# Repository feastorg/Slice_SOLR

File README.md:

<div align="center">
  <!-- Title: -->
  
  <h2><a href="https://github.com/uwo-fast/Slice_SOLR"> Slice SOLR </a></h2>
  <!-- Labels: -->
  <!-- First row: -->

  <a href="https://certification.oshwa.org/">
    
    <!-- img src="https://img.shields.io/badge/OSHWA-Certified-darkgreen?style=flat-square" height="20" alt="OSHWA" -->       <!-- img src="https://img.shields.io/badge/OSHWA-Pending-darkorange?style=flat-square" height="20" alt="OSHWA" -->
  </a>

  <!-- Second row: -->
  <br>

  <!-- Short description: -->
  <h3>Field Solar Power Slice for BREAD.</h3>
</div>

## Introduction
[Provide a brief introduction to the project, including the motivation and goals. Explain the significance and context of the research.]

## Project Overview
[Describe the project in more detail. This section can be split into subsections if necessary.]

## Installation
[Provide instructions for installing any necessary software or hardware components.]

## Usage
[Explain how to use the project. Include examples and screenshots if applicable.]

### Basic Usage
[Provide basic usage instructions.]

### Advanced Usage
[Provide advanced usage instructions, including any optional features or configurations.]

## Documentation
[Link to the detailed documentation if available. Provide instructions on how to access and navigate the documentation.]

## Contributing
[Explain how others can contribute to the project. Include guidelines for submitting issues, pull requests, and any coding standards.]

### Code of Conduct
[Link to the project's code of conduct if available.]

## License
[State the license under which the project is distributed. Include a link to the full license text.]

## Acknowledgements
[Acknowledge any contributors, collaborators, funding sources, or organizations that supported the project.]

## Contact
[Provide contact information for the project maintainer(s) or lead researcher(s). Include an email address or a link to a contact form.]

---

<div align="center">
  
</div>

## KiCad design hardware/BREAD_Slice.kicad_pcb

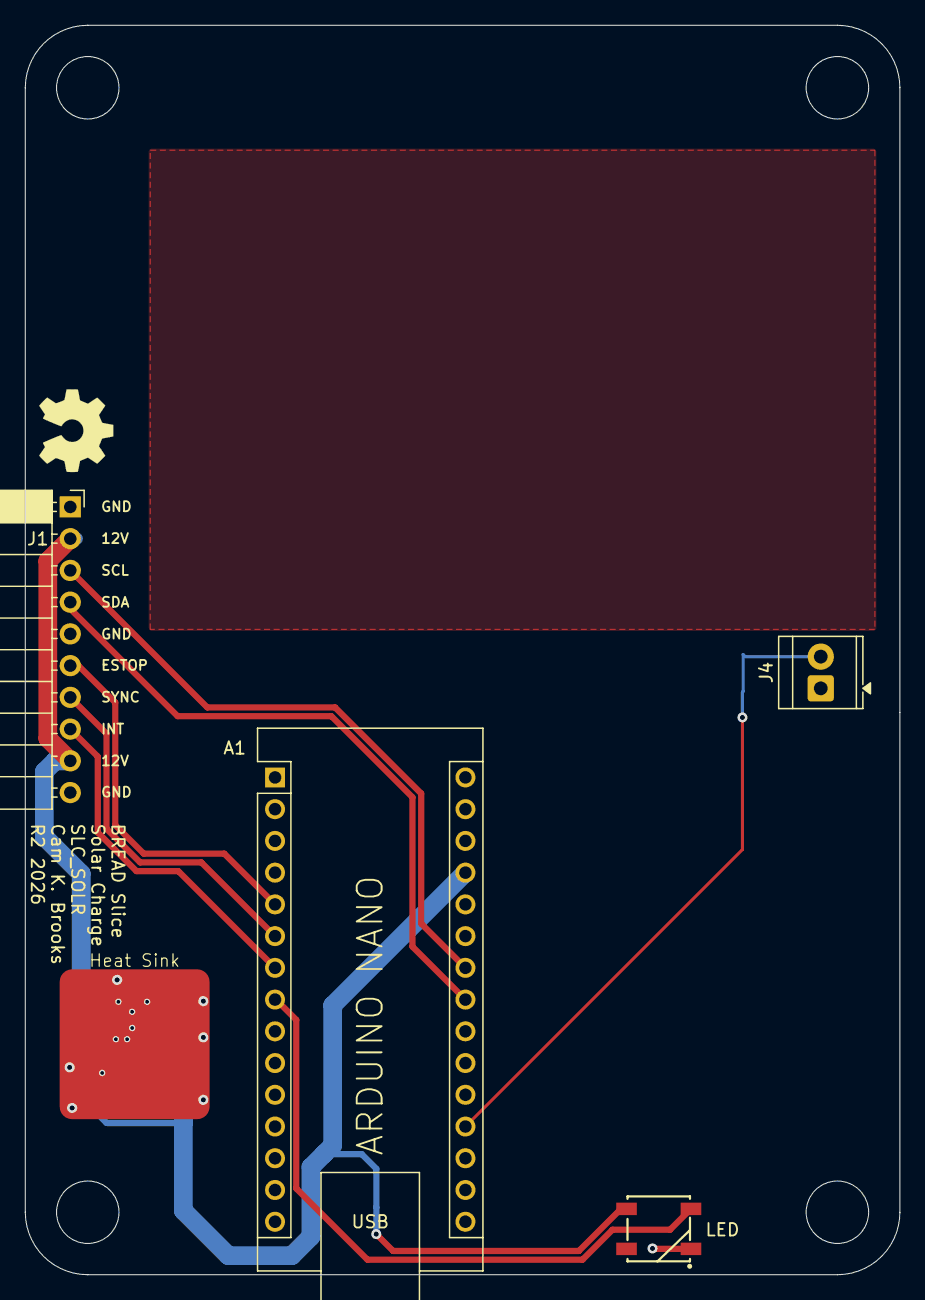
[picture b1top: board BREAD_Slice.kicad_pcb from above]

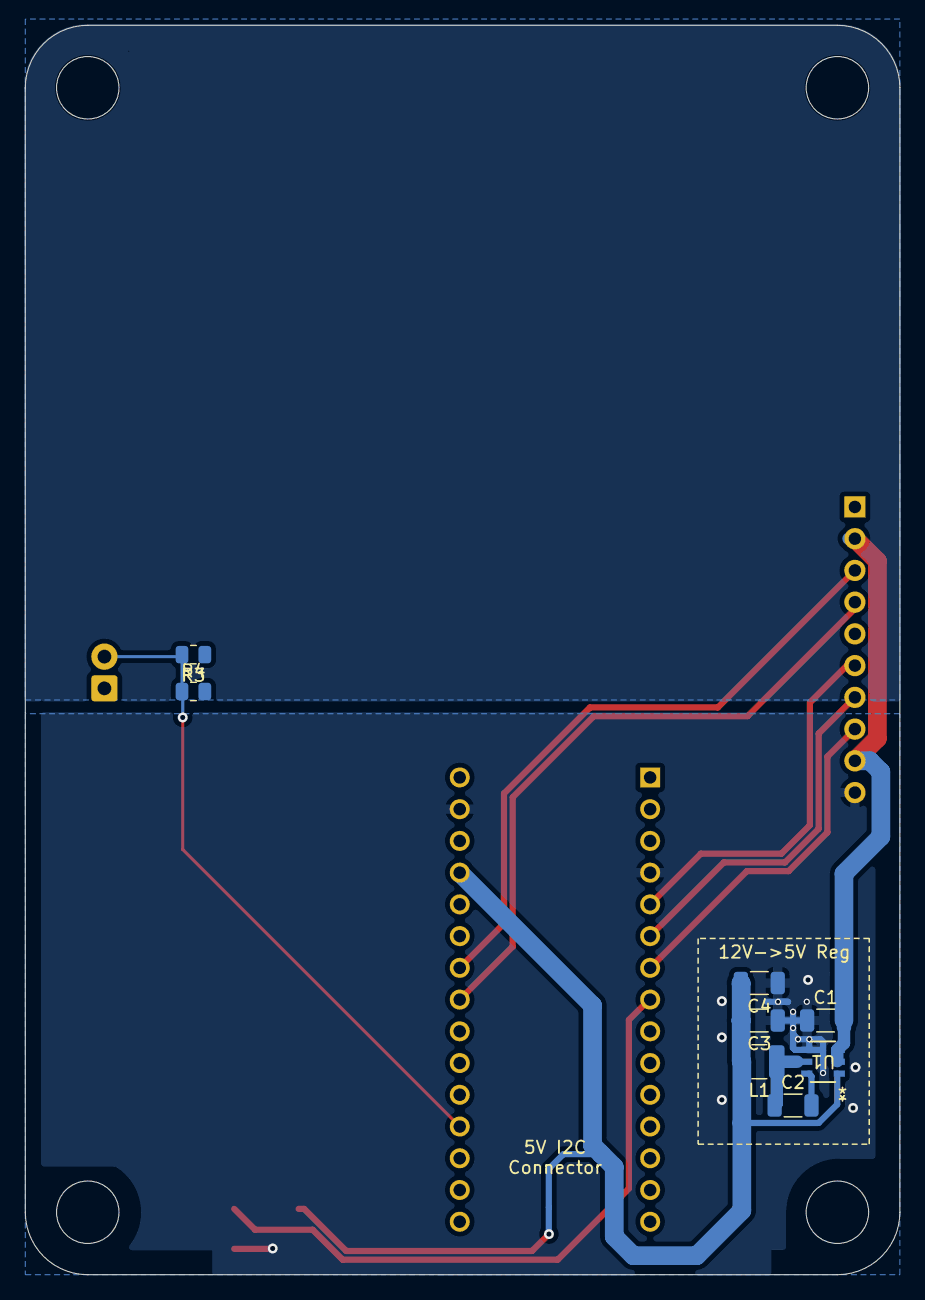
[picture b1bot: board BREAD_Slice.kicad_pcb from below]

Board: 2 copper layers, 70.0 x 100.0 mm, 18 parts (8 on the bottom side), 12 nets.

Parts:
A1: Arduino_Nano_v3.x; Arduino_Nano
C1, C3, C4: 22uF; C_1206_3216Metric
C2: 100nF; C_1206_3216Metric
D1: WS2812B_5050; WS2812-5050-4PIN
H1, H2, H3, H4: MountingHole; MountingHole_5mm
HS1: Heatsink_Pad; Thermal_Pad
J1: Conn_01x10_Female; PinSocket_1x10_P2.54mm_Horizontal
J4: Conn_01x02_Female; TerminalBlock_TE_282834-2_1x02_P2.54mm_Horizontal
L1: 4.7uH; L_1210_3225Metric
Logo1: Logo_Open_Hardware_Small; OSHW-Symbol_6.7x6mm_SilkScreen
R3: 5.23k; R_0805_2012Metric
R4: 30.1k; R_0805_2012Metric
U1: AP63205WU-7; SOIC_05WU-7_DIO

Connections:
+5V: A1.27 (+5V), C3.2, C4.2, D1.1 (VDD), L1.2, U1.1 (FB)
+12V: C1.2, J1.2, J1.9, U1.2 (EN), U1.3 (VIN)
/BAT_RTD: A1.19 (A0), J4.2, R3.2, R4.1
/E_STOP: A1.5 (D2), J1.6
/I2C_CLK: A1.24 (A5), J1.3
/I2C_DAT: A1.23 (A4), J1.4
/INT: A1.6 (D3), J1.7
/LED: A1.8 (D5), D1.4 (DIN)
/SYNC: A1.7 (D4), J1.8
GND: A1.4 (GND), A1.29 (GND), C1.1, C3.1, C4.1, D1.3 (VSS), HS1.1, J1.1, J1.5, J1.10, J4.1, R4.2, U1.4 (GND)
unnamed: C2.2, U1.6 (BST)
unnamed: C2.1, L1.1, U1.5 (SW)

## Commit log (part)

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2024-09-13 finished board
2024-09-30 JLCPCB order rev-A
2026-04-18 chore: clear out old backups
2026-05-20 Add slice.yaml manifest (schema v1.0)
2026-05-24 Add KiBot/docs pipeline
2026-05-24 Update TODO with CI findings
2026-05-24 Standardize TODO.md with Pass 1/Pass 2 structure
